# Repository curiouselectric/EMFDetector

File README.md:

# EMFDetector
A simple electro-magnetic field detector for viewing the unseen world around us.

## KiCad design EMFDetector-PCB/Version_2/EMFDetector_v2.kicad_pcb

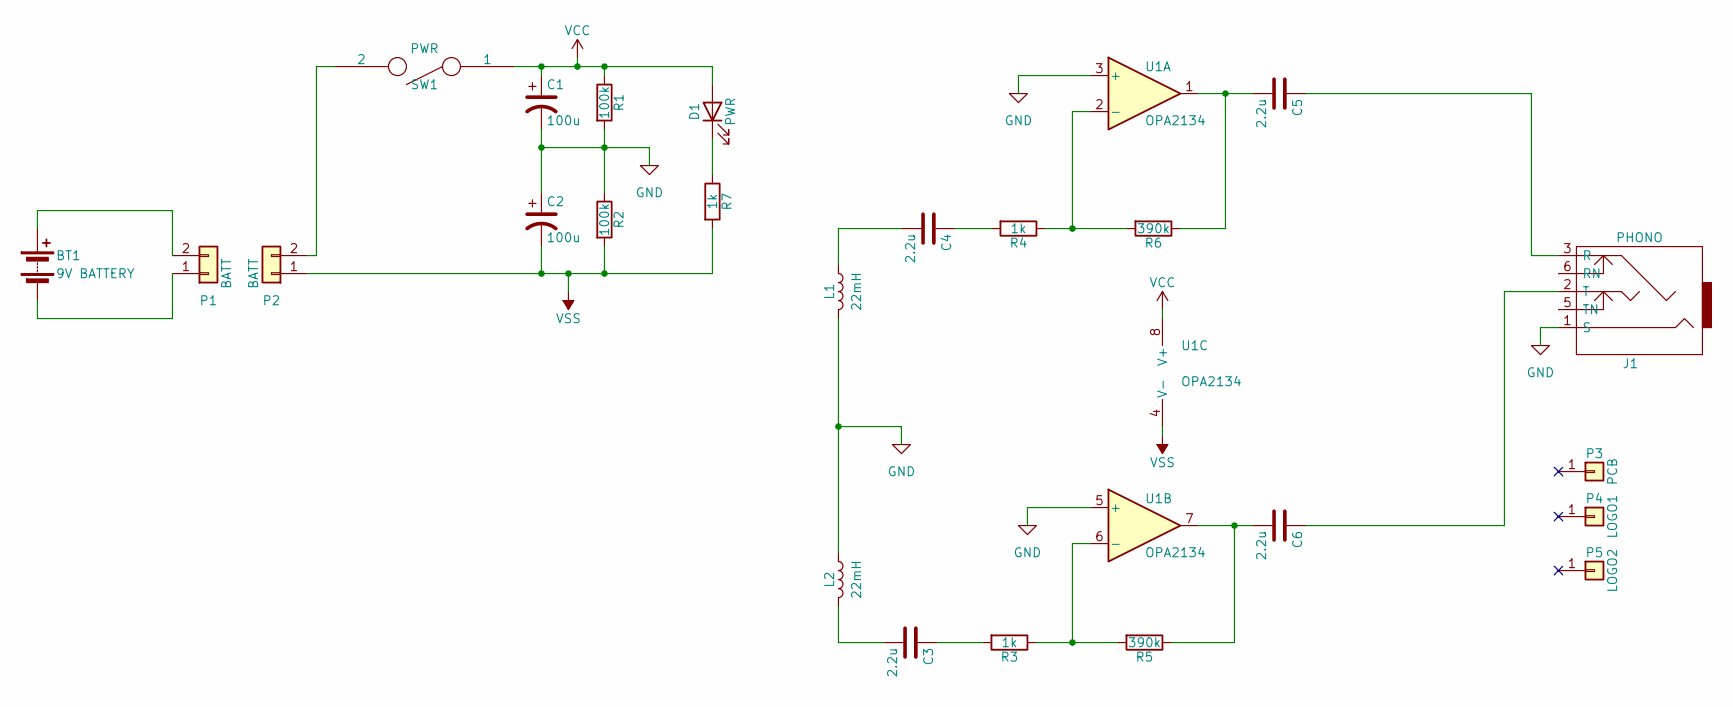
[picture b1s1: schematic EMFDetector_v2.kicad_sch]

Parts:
BT1: 9V BATTERY
C1, C2: 100u; C_1V7_TH
C3, C4, C5, C6: 2.2u; C1_wide_lg_pad
D1: PWR; TH_LED-5MM_larg_pad
J1: PHONO; TH_3_5mm_Jack_oval_holes
L1, L2: 22mH; TH_Inductor
P1: BATT
P2: BATT; Batt_Connector_Strain_Relief
P3: PCB; PCB_50x50mm
P4: LOGO1; TCEC_Words_13mm
P5: LOGO2; CuriousElectric_globe_10mm
R1, R2: 100k; TH_Resistor_1
R3, R4, R7: 1k; TH_Resistor_1
R5, R6: 390k; TH_Resistor_1
SW1: PWR; SW_SPDT_R_Angle_ALIEX
U1: OPA2134; DIP-8_300_ELL

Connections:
GND: C1.2, C2.1, J1.1 (S), L1.2, L2.1, R1.2, R2.1, U1.3 (+), U1.5 (+)
unnamed: BT1.1 (+), P1.2
unnamed: BT1.2 (-), P1.1
unnamed: C3.1, R3.2
unnamed: C3.2, L2.2
unnamed: C4.1, R4.2
unnamed: C4.2, L1.1
unnamed: C5.1, J1.3 (R)
unnamed: C5.2, R6.1, U1.1
unnamed: C6.1, J1.2 (T)
unnamed: C6.2, R5.1, U1.7
unnamed: D1.1 (K), R7.1
unnamed: P2.2, SW1.2
unnamed: R3.1, R5.2, U1.6 (-)
unnamed: R4.1, R6.2, U1.2 (-)
VCC: C1.1, D1.2 (A), R1.1, SW1.1, U1.8 (V+)
VSS: C2.2, P2.1, R2.2, R7.2, U1.4 (V-)

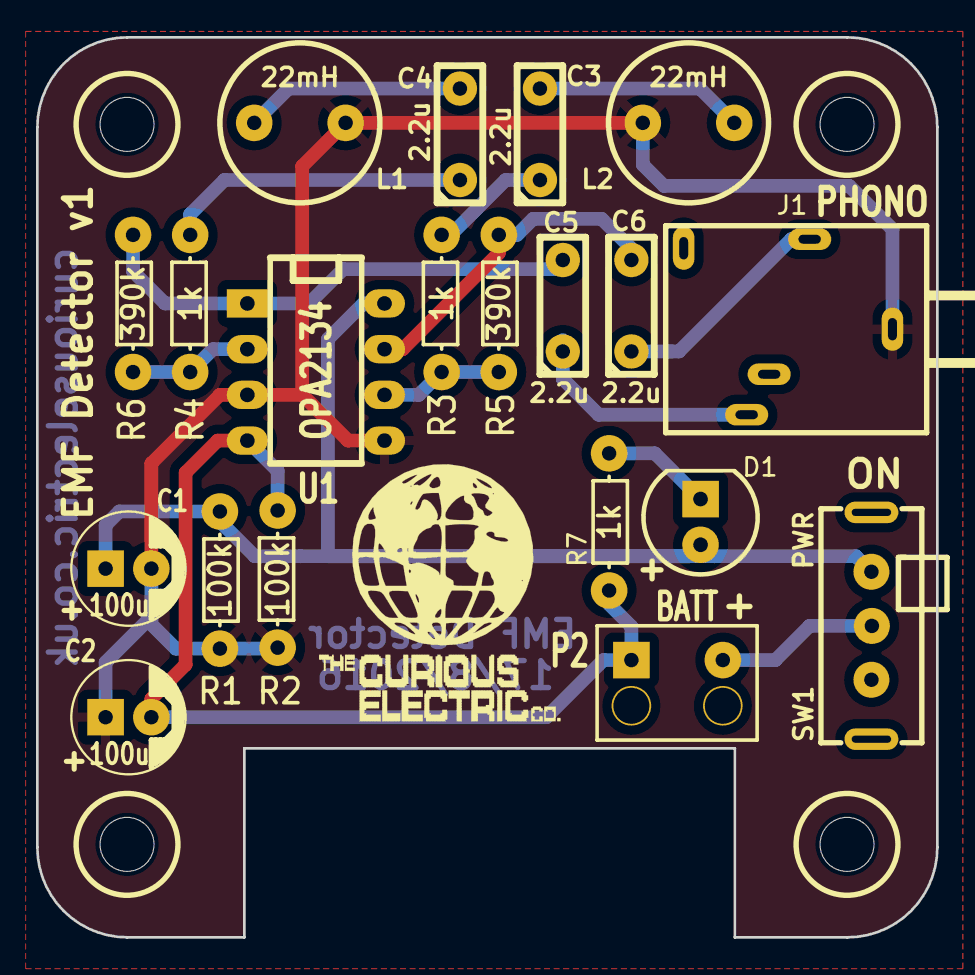
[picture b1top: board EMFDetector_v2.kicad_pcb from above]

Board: 2 copper layers, 50.0 x 50.0 mm, 23 parts (0 on the bottom side), 15 nets.

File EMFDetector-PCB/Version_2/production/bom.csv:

Designator,Footprint,Quantity,Value,LCSC Part #
"C1, C2",C_1V7_TH,2,100u,
"C3, C4, C5, C6",C1_wide_lg_pad,4,2.2u,
"L1, L2",TH_Inductor,2,22mH,
P2,Batt_Connector_Strain_Relief,1,BATT,
P4,TCEC_Words_13mm,1,LOGO1,
P5,CuriousElectric_globe_10mm,1,LOGO2,
"R1, R2",TH_Resistor_1,2,100k,
"R3, R4, R7",TH_Resistor_1,3,1k,
"R5, R6",TH_Resistor_1,2,390k,
SW1,SW_SPDT_R_Angle_ALIEX,1,PWR,
U1,DIP-8_300_ELL,1,OPA2134,

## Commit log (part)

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2017-03-24 First upload of info
2017-08-18 Updated instructions etc
2021-07-04 redone PCB with newer Kicad models
2021-07-25 New version of PCB built for new kicad version
2025-08-26 removed old instructions
2026-02-17 Updated enclosure files
